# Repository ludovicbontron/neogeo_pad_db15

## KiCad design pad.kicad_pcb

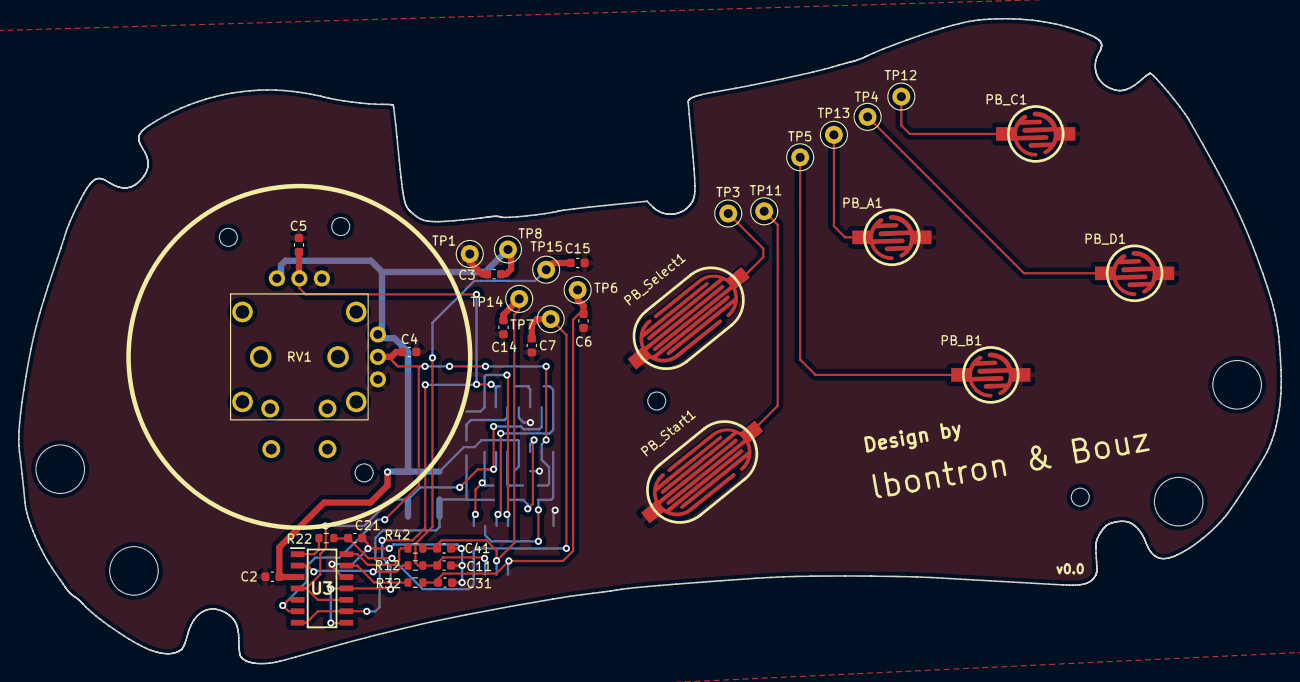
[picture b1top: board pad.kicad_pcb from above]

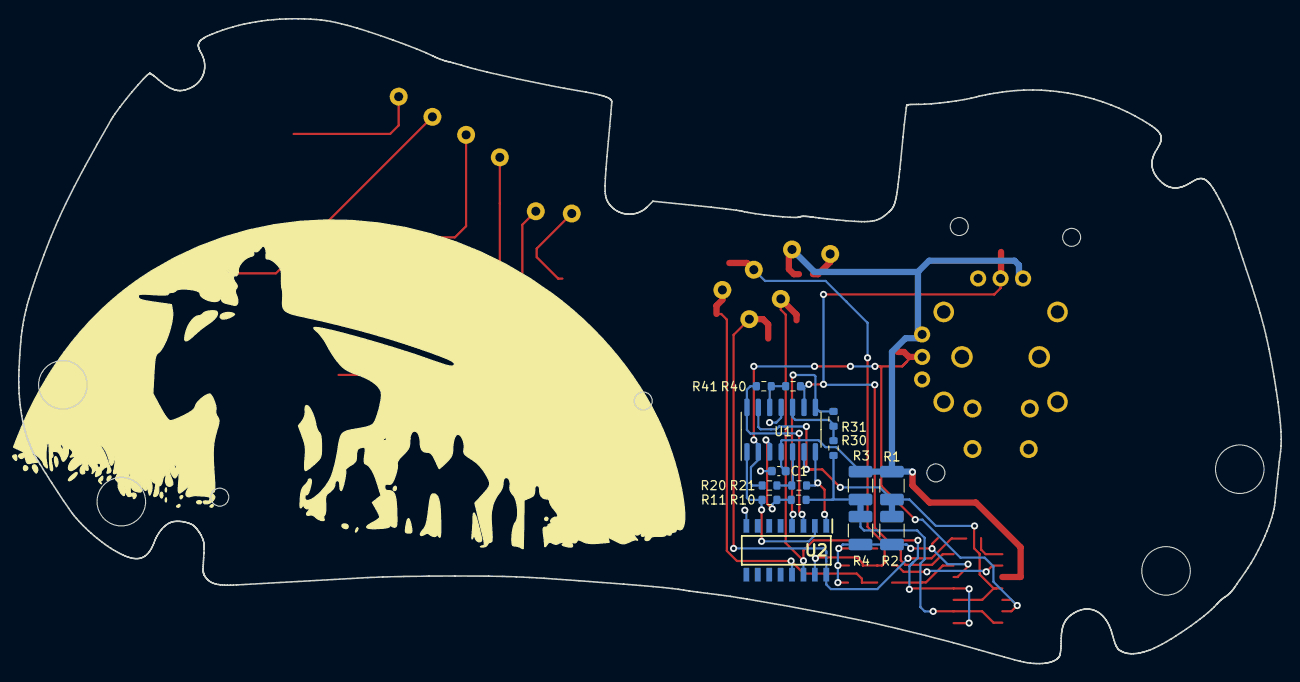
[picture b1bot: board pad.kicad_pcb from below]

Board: 2 copper layers, 140.4 x 71.7 mm, 51 parts (15 on the bottom side), 28 nets.

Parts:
C1, C2, C3, C4, C5, C6, C7, C11, C14, C15, C21, C31, C41: C; C_0603_1608Metric
PB_A1: SW_Push; button_A
PB_B1: SW_Push; button_A
PB_C1: SW_Push; button_A
PB_D1: SW_Push; button_A
PB_Select1: SW_Push; button_start
PB_Start1: SW_Push; button_start
R1, R2, R3, R4: R; R_1210_3225Metric_Pad1.30x2.65mm_HandSolder
R10, R11, R12, R20, R21, R22, R30, R31, R32, R40, R41, R42: R; R_0603_1608Metric
RV1: RKJXV122400R; RKJXV122400R_joystick
TP1: db15.1_GND; TestPoint_Loop_D1.80mm_Drill1.0mm_Beaded
TP3: db15.3_Select; TestPoint_Loop_D1.80mm_Drill1.0mm_Beaded
TP4: db15.4_ButtonD; TestPoint_Loop_D1.80mm_Drill1.0mm_Beaded
TP5: db15.5_ButtonB; TestPoint_Loop_D1.80mm_Drill1.0mm_Beaded
TP6: db15.6_Right; TestPoint_Loop_D1.80mm_Drill1.0mm_Beaded
TP7: db15.7_Bottom; TestPoint_Loop_D1.80mm_Drill1.0mm_Beaded
TP8: db15.8_5V; TestPoint_Loop_D1.80mm_Drill1.0mm_Beaded
TP11: db15.11_Start; TestPoint_Loop_D1.80mm_Drill1.0mm_Beaded
TP12: db15.12_ButtonC; TestPoint_Loop_D1.80mm_Drill1.0mm_Beaded
TP13: db15.13_ButtonA; TestPoint_Loop_D1.80mm_Drill1.0mm_Beaded
TP14: db15.14_Left; TestPoint_Loop_D1.80mm_Drill1.0mm_Beaded
TP15: db15.15_Top; TestPoint_Loop_D1.80mm_Drill1.0mm_Beaded
U1: LPV324MX; SOIC-14_3.9x8.7mm_P1.27mm
U2: ULN2002; SOIC127P600X175-16N
U3: LM339; SOIC127P600X175-14N

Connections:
+5V: C1.1, C2.1, C3.1, R1.2, R3.2, RV1.1, RV1.4, TP8.1, U1.4 (V+), U3.3 (V+)
BotButton: R21.2, U1.7, U2.1 (I1)
GND: C1.2, C2.2, C3.2, C4.2, C5.2, C6.2, C7.2, C11.2, C14.2, C15.2, C21.2, C31.2, C41.2, PB_A1.1, PB_B1.1, PB_C1.1, PB_D1.1, PB_Select1.1, PB_Start1.1, R2.1, R4.1, RV1.3, RV1.6, TP1.1, U1.11 (V-), U2.8 (GND), U3.12 (V-)
LefButton: R41.2, U1.14, U2.3 (I3)
unnamed: PB_A1.2, TP13.1
unnamed: PB_B1.2, TP5.1
unnamed: PB_C1.2, TP12.1
unnamed: PB_D1.2, TP4.1
unnamed: PB_Select1.2, TP3.1
unnamed: PB_Start1.2, TP11.1
unnamed: R10.2, R11.1, U1.3 (+)
unnamed: R12.1, U3.2
unnamed: R20.2, R21.1, U1.5 (+)
unnamed: R22.1, U3.1
unnamed: R30.2, R31.1, U1.10 (+)
unnamed: R32.1, U3.13
unnamed: R40.2, R41.1, U1.12 (+)
unnamed: R42.1, U3.14
RigButton: R31.2, U1.8, U2.4 (I4)
TP6_RIG: C6.1, C31.1, R32.2, TP6.1, U2.13 (O4)
TP7_BOT: C7.1, C21.1, R22.2, TP7.1, U2.16 (O1)
TP14_LEF: C14.1, C41.1, R42.2, TP14.1, U2.14 (O3)
TP15_TOP: C11.1, C15.1, R12.2, TP15.1, U2.15 (O2)
TopButton: R11.2, U1.1, U2.2 (I2)
VRef_n: R3.1, R4.2, R10.1, R30.1, U3.7 (+), U3.9 (+)
VRef_p: R1.1, R2.2, U1.6 (-), U1.13 (-), U3.4 (-), U3.10 (-)
xAxis: C4.1, R20.1, RV1.5, U1.2 (-), U3.5 (+), U3.6 (-)
yAxis: C5.1, R40.1, RV1.2, U1.9 (-), U3.8 (-), U3.11 (+)

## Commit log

2022-12-06 First commit: base of schematic
2022-12-07 Update schematic with some footprinit
2022-12-07 Add push button on the footprint
2022-12-12 Update schematic and board. All implemented, but not tested. Mechanical not tested yet
2022-12-12 Update lib to update pad polygon
2022-12-15 Update board size
2023-01-09 todo: clean up and verify me
